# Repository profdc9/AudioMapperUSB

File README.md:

# AudioMapper USB by Daniel Marks

This project is to develop a simple device for characterizing the audio characteristics of a room.  It is intended to be used 

It is based on the PCM2900/PCM2902 TI USB CODEC DAC/ADC.  It has the following features:

- Amplification for two microphone inputs (up to a gain of 125 or 42 dB gain).  The gain stages may be jumpered out if desired to provide a standard line input.
- Phantom power provided to microphone inputs (10 kohm resistor for 5 volts) so that electret or dynamic microphones may be used.
- DAC is 44.1 kHz/48 kHz 16-bit stereo output.
- ADC is 44.1 kHz/48 kHz 16-bit stereo input.
- Can sample the outputs back to the input for synchronizing the audio output signal to the audio input signal.
- Several boards may be chained together to synchronize them.
- A provision for external power input so that the USB power noise (especially USB traffic) does not produce noise on the microphone inputs.  It is recommended that a 9-12 VDC linear power supply is used.
- SPDIF input and outputs.
- Feedback resistors can be surface mount or through hole for easy gain adjustments.

The kicad files and gerbers are provided.  The project is licensed under the Creative Common License, CC-BY-SA 4.0.

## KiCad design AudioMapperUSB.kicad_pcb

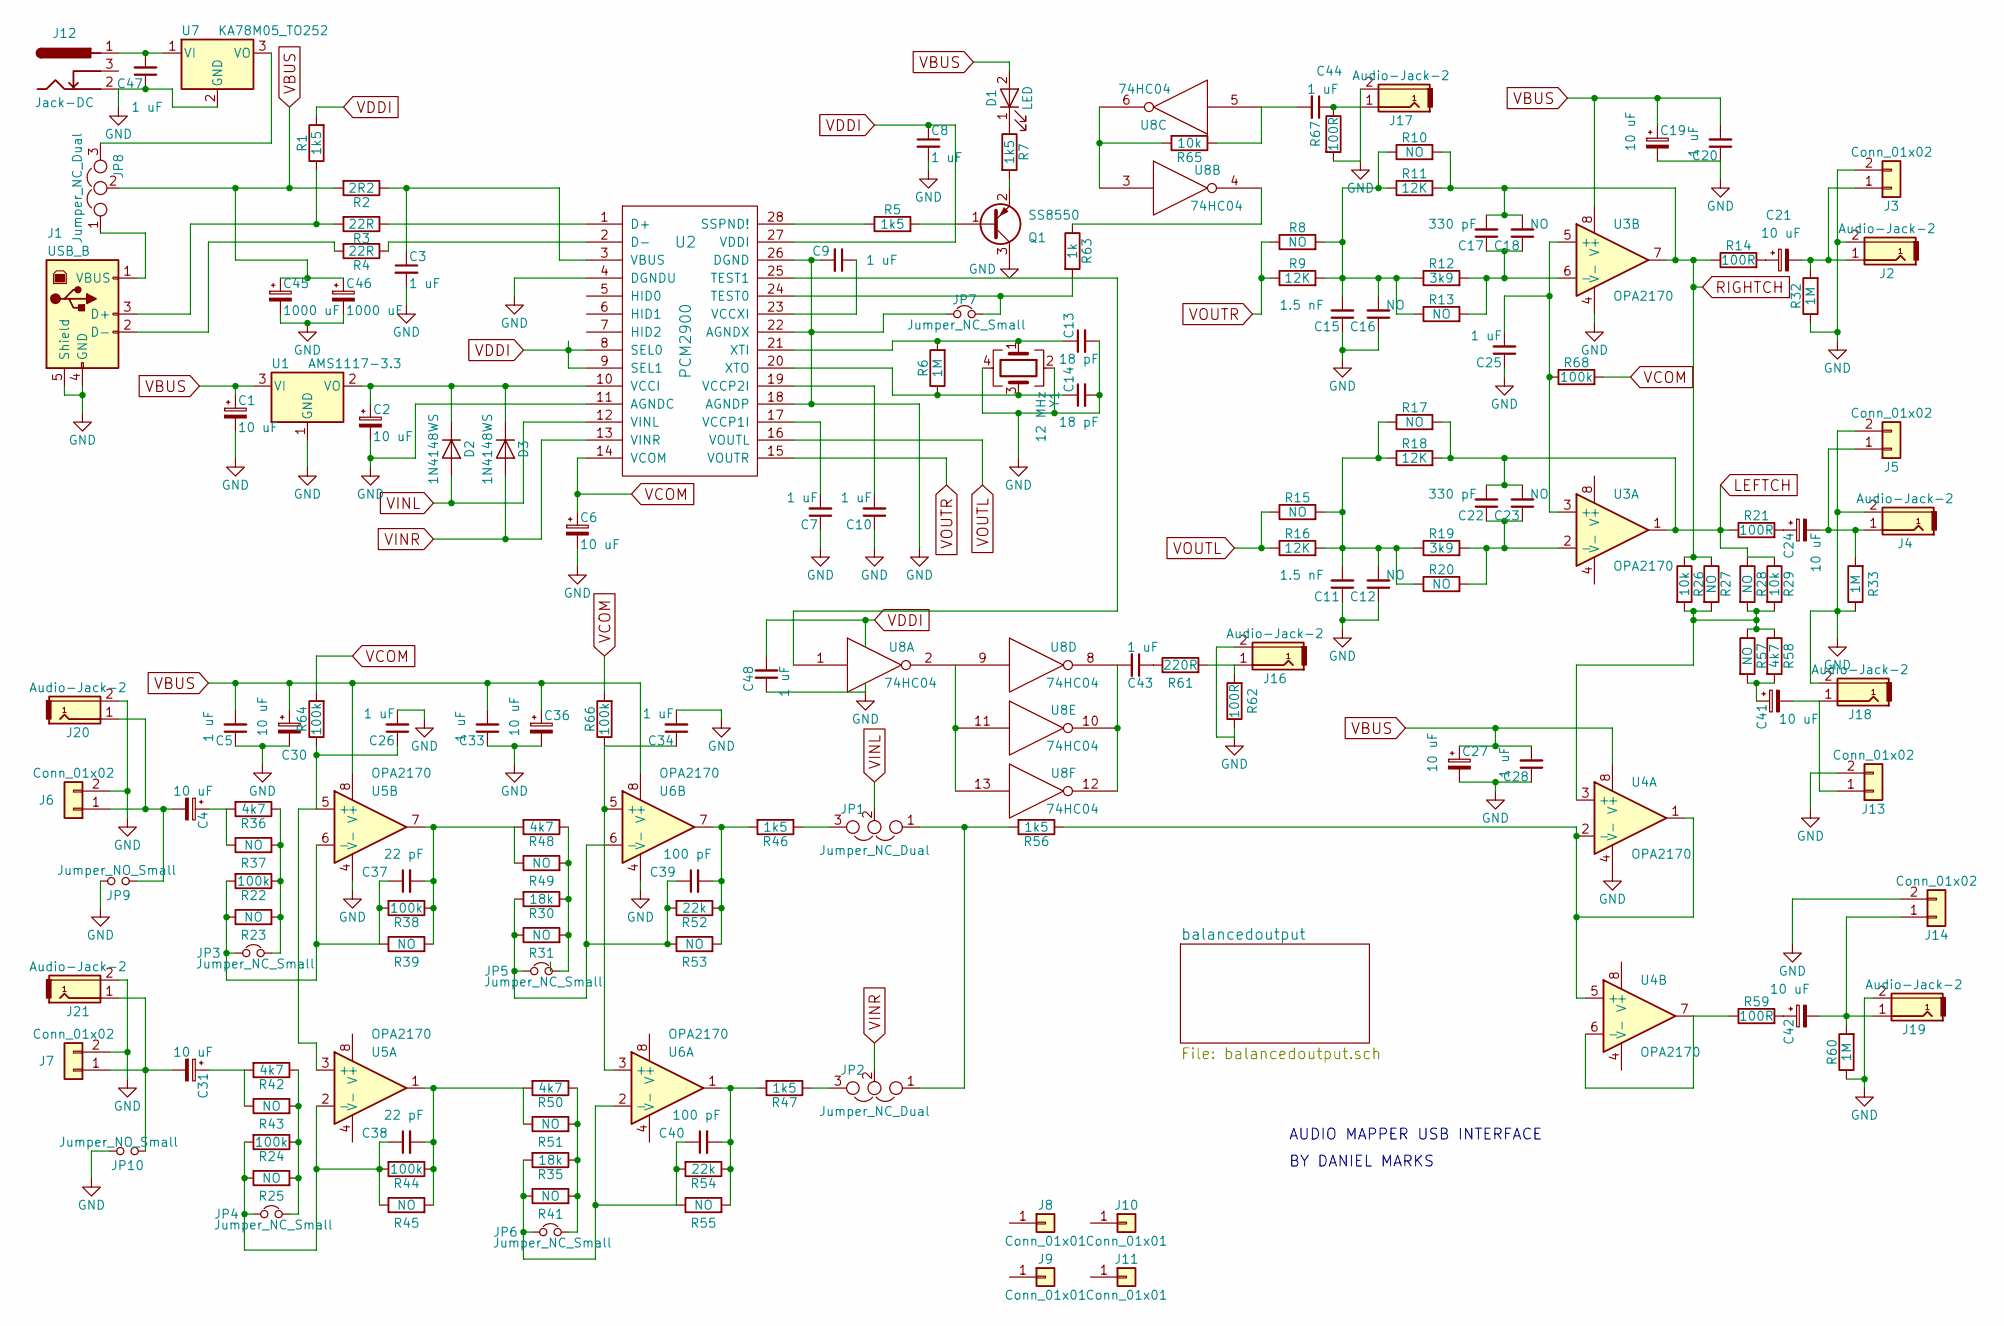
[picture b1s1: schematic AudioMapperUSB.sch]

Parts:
C1, C2, C4, C6, C19, C21, C24, C27, C30, C31, C36, C41, C42: 10 uF; CP_1206_HandSoldering; LCSC C7171
C3, C5, C7, C8, C9, C10, C20, C25, C26, C28, C33, C34, C43, C44, C47, C48: 1 uF; C_0805_HandSoldering; LCSC C28323
C11, C15: 1.5 nF; C_0805_HandSoldering; LCSC C1717
C12, C16: NO; C_Disc_D5.0mm_W2.5mm_P5.00mm
C13, C14: 18 pF; C_0805_HandSoldering; LCSC C1797
C17, C22: 330 pF; C_0805_HandSoldering; LCSC C51207
C18, C23: NO; C_Disc_D5.0mm_W2.5mm_P5.00mm; LCSC C51207
C37, C38: 22 pF; C_0805_HandSoldering; LCSC C1804
C39, C40: 100 pF; C_0805_HandSoldering; LCSC C1790
C45, C46: 1000 uF; CP_Radial_D10.0mm_P5.00mm
D1: LED; LED_0805_HandSoldering; LCSC C84256
D2, D3: 1N4148WS; D_SOD-323_HandSoldering; LCSC C2128
J1: USB_B
J2, J4, J16, J17, J18, J19, J20, J21: Audio-Jack-2; RCAConnectorCommon
J3, J5, J6, J7, J13, J14: Conn_01x02; TerminalBlock_bornier-2_P5.08mm
J8, J9, J10, J11: Conn_01x01; 1pin
J12: Jack-DC; BARREL_JACK
JP1, JP2, JP8: Jumper_NC_Dual; Pin_Header_Straight_1x03_Pitch2.54mm
JP3, JP4, JP5, JP6, JP7: Jumper_NC_Small; Pin_Header_Straight_1x02_Pitch2.54mm
JP9, JP10: Jumper_NO_Small; Pin_Header_Straight_1x02_Pitch2.54mm
Q1: SS8550; SOT-23; LCSC C8542
R1, R5, R7, R46, R47, R56: 1k5; R_0805_HandSoldering; LCSC C4310
R2: 2R2; R_0805_HandSoldering; LCSC C17521
R3, R4: 22R; R_0805_HandSoldering; LCSC C17561
R6, R32, R33, R60: 1M; R_0805_HandSoldering; LCSC C17514
R8, R10, R13, R15, R17, R20, R23, R25, R27, R28, R31, R37, R39, R41, R43, R45, R49, R51, R53, R55, R57: NO; R_Axial_DIN0207_L6.3mm_D2.5mm_P7.62mm_Horizontal
R9, R11, R16: 12K; R_0805_HandSoldering; LCSC C17444
R12, R19: 3k9; R_0805_HandSoldering; LCSC C17614
R14, R21, R59, R62, R67: 100R; R_0805_HandSoldering; LCSC C17408
R18: 12K; R_0805_HandSoldering; LCSC C17614
R22, R24, R38, R44, R64, R66, R68: 100k; R_0805_HandSoldering; LCSC C17407
R26, R29, R65: 10k; R_0805_HandSoldering; LCSC C17414
R30, R35: 18k; R_0805_HandSoldering; LCSC C17506
R36, R42, R48, R50, R58: 4k7; R_0805_HandSoldering; LCSC C17673
R52, R54: 22k; R_0805_HandSoldering; LCSC C17560
R61: 220R; R_0805_HandSoldering; LCSC C17557
R63: 1k; R_0805_HandSoldering; LCSC C17513
U1: AMS1117-3.3; SOT-223-3_TabPin2; LCSC C6186
U2: PCM2900; SSOP-28_5.3x10.2mm_Pitch0.65mm; LCSC C180425
U3, U4, U5, U6: OPA2170; SOIC-8_3.9x4.9mm_Pitch1.27mm; LCSC C56285
U7: KA78M05_TO252; TO-252-3_TabPin2; LCSC C58069
U8: 74HC04; SOIC-14_3.9x8.7mm_Pitch1.27mm; LCSC C5590
Y1: 12 MHz; Crystal_SMD_3225-4pin_3.2x2.5mm_HandSoldering; LCSC C9002

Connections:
GND: C1.2, C2.2, C3.2, C5.1, C6.2, C7.1, C8.2, C9.2, C10.1, C11.1, C12.1, C13.2, C14.2, C15.1, C16.1, C19.2, C20.1, C25.1, C26.2, C27.2, C28.1, C30.2, C33.1, C34.2, C36.2, C45.2, C46.2, C47.1, C48.1, J1.4 (GND), J1.5 (Shield), J2.2, J3.2, J4.2, J5.2, J6.2, J7.2, J12.2, J13.2, J14.2, J16.2, J17.2, J18.2, J19.2, J20.2, J21.2, JP7.1, JP9.2, JP10.2, Q1.3 (C), R32.1, R33.1, R60.1, R62.1, R67.2, U1.1 (GND), U2.4 (DGNDU), U2.11 (AGNDC), U2.18 (AGNDP), U2.22 (AGNDX), U2.26 (DGND), U3.4 (V-), U4.4 (V-), U5.4 (V-), U6.4 (V-), U7.2 (GND), U8.7 (GND), Y1.2, Y1.4; also elsewhere on the board
LEFTCH: C22.2, C23.2, R17.2, R18.2, R21.1, R28.1, R29.1, U3.1; also elsewhere on the board
unnamed: C2.1, D2.1 (K), D3.1 (K), U1.2 (VO), U2.10 (VCCI)
unnamed: C3.1, R2.1, U2.3 (VBUS)
unnamed: C4.1, R36.2, R37.1
unnamed: C4.2, J6.1, J20.1, JP9.1
unnamed: C7.2, U2.17 (VCCP1I)
unnamed: C9.1, U2.23 (VCCXI)
unnamed: C10.2, U2.19 (VCCP2I)
unnamed: C11.2, C12.2, R15.2, R16.2, R17.1, R18.1, R19.1, R20.1
unnamed: C13.1, R6.2, U2.21 (XTI), Y1.1
unnamed: C14.1, R6.1, U2.20 (XTO), Y1.3
unnamed: C15.2, C16.2, R8.2, R9.2, R10.1, R11.1, R12.1, R13.1
unnamed: C17.1, C18.1, R12.2, R13.2, U3.6 (-)
unnamed: C21.1, R14.2
unnamed: C21.2, J2.1, J3.1, R32.2
unnamed: C22.1, C23.1, R19.2, R20.2, U3.2 (-)
unnamed: C24.1, R21.2
unnamed: C24.2, J4.1, J5.1, R33.2
unnamed: C25.2, R68.1, U3.3 (+), U3.5 (+)
unnamed: C26.1, R64.1, U5.3 (+), U5.5 (+)
unnamed: C31.1, R42.2, R43.1
unnamed: C31.2, J7.1, J21.1, JP10.1
unnamed: C34.1, R66.1, U6.3 (+), U6.5 (+)
unnamed: C37.1, JP3.1, R22.2, R23.1, R38.2, R39.1, U5.6 (-)
unnamed: C37.2, R38.1, R39.2, R48.2, R49.1, U5.7
unnamed: C38.1, JP4.1, R24.2, R25.1, R44.2, R45.1, U5.2 (-)
unnamed: C38.2, R44.1, R45.2, R50.2, R51.1, U5.1
unnamed: C39.1, JP5.1, R30.2, R31.1, R52.2, R53.1, U6.6 (-)
unnamed: C39.2, R46.2, R52.1, R53.2, U6.7
unnamed: C40.1, JP6.1, R35.2, R41.1, R54.2, R55.1, U6.2 (-)
unnamed: C40.2, R47.2, R54.1, R55.2, U6.1
unnamed: C41.1, R57.2, R58.2
unnamed: C41.2, J13.1, J18.1
unnamed: C42.1, R59.2
unnamed: C42.2, J14.1, J19.1, R60.2
unnamed: C43.1, R61.1
unnamed: C43.2, U8.8, U8.10, U8.12
unnamed: C44.1, J17.1, R67.1
unnamed: C44.2, R65.1, U8.5
unnamed: C47.2, J12.1, U7.1 (VI)
unnamed: D1.1 (K), R7.1
unnamed: J1.1 (VBUS), JP8.1
unnamed: J1.2 (D-), R4.2
unnamed: J1.3 (D+), R1.1, R3.2
unnamed: J16.1, R61.2, R62.2
unnamed: JP1.1, JP2.1, R56.2
unnamed: JP1.3, R46.1
unnamed: JP2.3, R47.1
unnamed: JP3.2, R22.1, R23.2, R36.1, R37.2
unnamed: JP4.2, R24.1, R25.2, R42.1, R43.2
unnamed: JP5.2, R30.1, R31.2, R48.1, R49.2
unnamed: JP6.2, R35.1, R41.2, R50.1, R51.2
unnamed: JP7.2, R63.2, U2.24 (TEST0)
unnamed: JP8.3, U7.3 (VO)
unnamed: Q1.1 (B), R5.2
unnamed: Q1.2 (E), R7.2
unnamed: R3.1, U2.1 (D+)
unnamed: R4.1, U2.2 (D-)
unnamed: R5.1, U2.28 (SSPND!)
unnamed: R26.2, R27.2, R28.2, R29.2, R57.1, R58.1, U4.3 (+)
unnamed: R56.1, U4.1, U4.2 (-), U4.5 (+)
unnamed: R59.1, U4.6 (-), U4.7
unnamed: R63.1, U8.4
unnamed: R65.2, U8.3, U8.6
unnamed: U2.25 (TEST1), U8.1
unnamed: U8.2, U8.9, U8.11, U8.13
RIGHTCH: C17.2, C18.2, R10.2, R11.2, R14.1, R26.1, R27.1, U3.7; also elsewhere on the board
VBUS: C1.1, C5.2, C19.1, C20.2, C27.1, C28.2, C30.1, C33.2, C36.1, C45.1, C46.1, D1.2 (A), JP8.2, R2.2, U1.3 (VI), U3.8 (V+), U4.8 (V+), U5.8 (V+), U6.8 (V+); also elsewhere on the board
VCOM: C6.1, R64.2, R66.2, R68.2, U2.14 (VCOM); also elsewhere on the board
VDDI: C8.1, C48.2, R1.2, U2.8 (SEL0), U2.9 (SEL1), U2.27 (VDDI), U8.14 (VCC)
VINL: D2.2 (A), JP1.2, U2.12 (VINL)
VINR: D3.2 (A), JP2.2, U2.13 (VINR)
VOUTL: R15.1, R16.1, U2.16 (VOUTL)
VOUTR: R8.1, R9.1, U2.15 (VOUTR)

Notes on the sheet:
AUDIO MAPPER USB INTERFACE
BY DANIEL MARKS

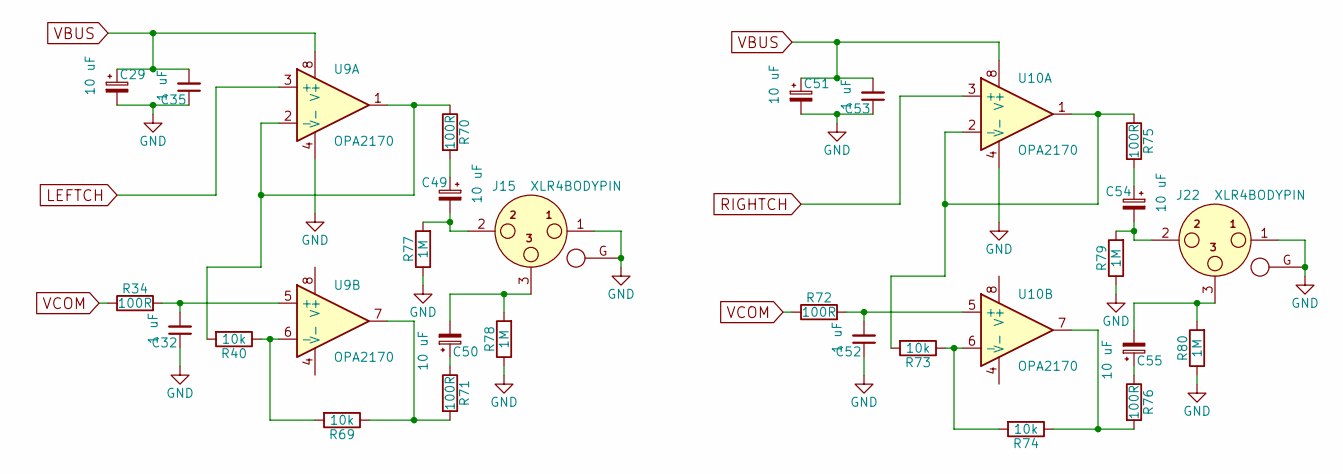
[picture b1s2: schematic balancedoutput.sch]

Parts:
C29, C49, C50, C51, C54, C55: 10 uF; CP_1206_HandSoldering; LCSC C7171
C32, C35, C52, C53: 1 uF; C_0805_HandSoldering; LCSC C28323
J15, J22: XLR4BODYPIN; IOXLR3MEH
R34, R70, R71, R72, R75, R76: 100R; R_0805_HandSoldering; LCSC C17408
R40, R69, R73, R74: 10k; R_0805_HandSoldering; LCSC C17414
R77, R78, R79, R80: 1M; R_0805_HandSoldering; LCSC C17514
U9, U10: OPA2170; SOIC-8_3.9x4.9mm_Pitch1.27mm; LCSC C56285

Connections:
GND: C29.2, C32.1, C35.1, C51.2, C52.1, C53.1, J15.1, J15.G, J22.1, J22.G, R77.1, R78.1, R79.1, R80.1, U9.4 (V-), U10.4 (V-); also elsewhere on the board
LEFTCH: U9.3 (+); also elsewhere on the board
unnamed: C32.2, R34.2, U9.5 (+)
unnamed: C49.1, R70.2
unnamed: C49.2, J15.2, R77.2
unnamed: C50.1, R71.1
unnamed: C50.2, J15.3, R78.2
unnamed: C52.2, R72.2, U10.5 (+)
unnamed: C54.1, R75.2
unnamed: C54.2, J22.2, R79.2
unnamed: C55.1, R76.1
unnamed: C55.2, J22.3, R80.2
unnamed: R40.1, R69.2, U9.6 (-)
unnamed: R40.2, R70.1, U9.1, U9.2 (-)
unnamed: R69.1, R71.2, U9.7
unnamed: R73.1, R74.2, U10.6 (-)
unnamed: R73.2, R75.1, U10.1, U10.2 (-)
unnamed: R74.1, R76.2, U10.7
RIGHTCH: U10.3 (+); also elsewhere on the board
VBUS: C29.1, C35.2, C51.1, C53.2, U9.8 (V+), U10.8 (V+); also elsewhere on the board
VCOM: R34.1, R72.1; also elsewhere on the board

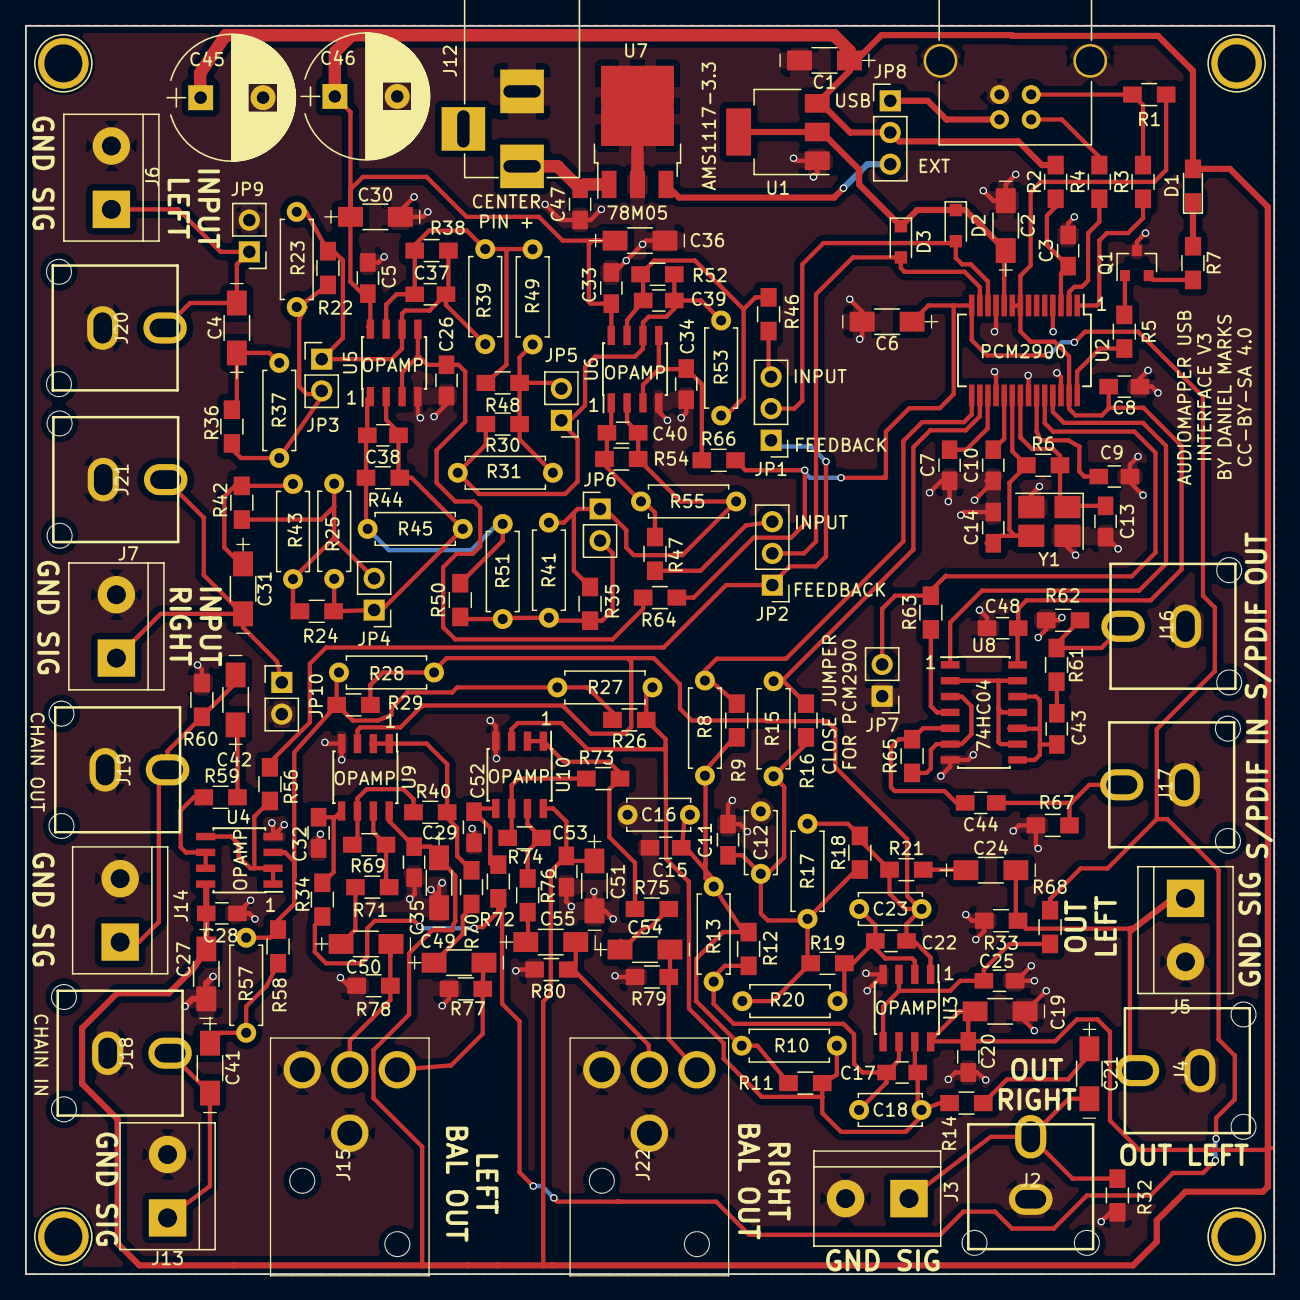
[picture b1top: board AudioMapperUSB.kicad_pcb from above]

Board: 2 copper layers, 100.0 x 100.0 mm, 182 parts (0 on the bottom side), 91 nets.

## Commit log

2020-12-29 Added second gain stage to microphone
2020-12-31 Added antialiasing on input and SP/DIF input/output
2021-01-01 Added ability to chain outputs of two boards together
2021-01-03 Added real circuit to interface SPDIF levels to 3.3 V CMOS levels
2021-01-03 Added pulldown resistor to input
2021-01-06 Fixed backward polarity audio connectors. Duh.
2021-01-15 Added external power
2021-01-16 Use inverter for SPDIF
2021-01-16 Show picture
2021-01-17 Fixed problem with VCOM leaking into input audio
2021-01-20 Added isolation between phantom power in mic channels
2021-02-01 JLCPCB order 2021-01-31
2021-02-11 Added source code of Audiomapper
2021-02-11 Didnt get checked in with license
2021-02-12 Added enable/disable microphone position
2021-02-26 Fixed JLCPCB BOM/placement
2021-03-22 Added balanced outputs
